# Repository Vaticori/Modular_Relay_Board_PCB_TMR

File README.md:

# Modular Relay Board TMR
A 4 channel relay board made for the Toronto Metropolitan Robotics team for higher voltage inputs to be switched using the onboard Teensy 4.1 MCU. 
I have linked the 3D model below, and a high resolution pdf of the schematic can be found in the repository. 

# [View Interactive 3D Model of my PCB!](https://skfb.ly/pACNG)

## Schematic

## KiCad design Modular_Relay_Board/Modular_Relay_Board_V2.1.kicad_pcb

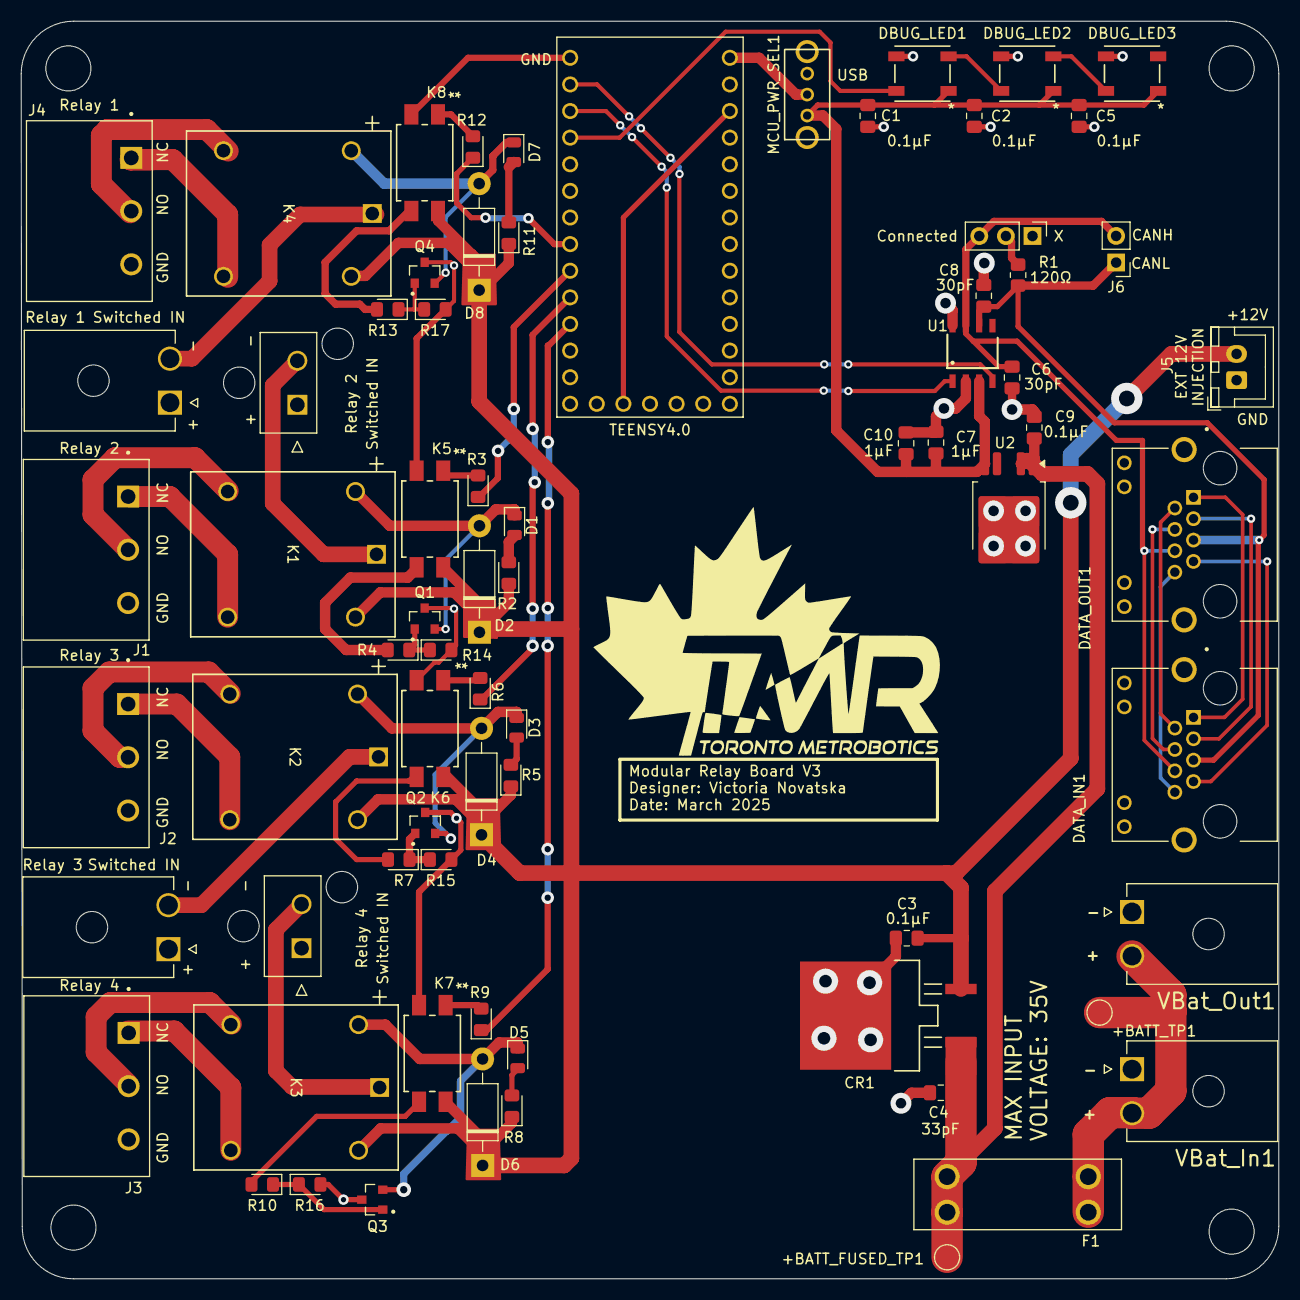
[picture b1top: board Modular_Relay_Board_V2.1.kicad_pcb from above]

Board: 2 copper layers, 120.0 x 120.0 mm, 73 parts (0 on the bottom side), 57 nets.

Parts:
+BATT_FUSED_TP1: TestPoint; TestPoint_Pad_D2.0mm
+BATT_TP1: TestPoint; TestPoint_Pad_D2.0mm
C1, C2, C3, C5, C7, C9: CL21B104KBCNNNC; C_0805_2012Metric_Pad1.18x1.45mm_HandSolder
C4: CC0805JRNPO9BN330; C_0805_2012Metric_Pad1.18x1.45mm_HandSolder
C6, C8: 0805CG300J500NT; C_0805_2012Metric_Pad1.18x1.45mm_HandSolder
C10: CL21B105KAFNFNE; C_0805_2012Metric_Pad1.18x1.45mm_HandSolder
CR1: C13456; D2PAK_STM
D1, D3, D5, D7: KT-0805Y; LED_0805_2012Metric
D2, D4, D6, D8: 1N4007; D_DO-41_SOD81_P10.16mm_Horizontal
DATA_IN1: MTJ-88ARX1-FSM-LG; ADAMTECH_MTJ-88ARX1-FSM-LG
DATA_OUT1: MTJ-88ARX1-FSM-LG; ADAMTECH_MTJ-88ARX1-FSM-LG
DBUG_LED1, DBUG_LED2, DBUG_LED3: COM-16347; COM-16347_SPK-M
F1: 3557-2; FUSE_3557-2
J1, J2, J3, J4: 1757255; PHOENIX_1757255
J5: JST XH; JST_XH_B2B-XH-A_1x02_P2.50mm_Vertical
J6: Conn_01x02_Pin; PinHeader_1x02_P2.54mm_Vertical
K1, K2, K3, K4: AZ943-1CH-12DE; AZ943-1CH_AMZ
K5, K6, K7, K8: LTV-816S-TA1-A; LTV-816S_LTO
MCU_PWR_SEL1: OS102011MS2QN1
Q1, Q2, Q3, Q4: 2N7002; TRANS_2N7002
R1: 0805W8F1200T5E; R_0805_2012Metric_Pad1.20x1.40mm_HandSolder
R2, R3, R4, R5, R6, R7, R8, R9, R10, R11, R12, R13: 0805W8F1001T5E; LED_0805_2012Metric_Pad1.15x1.40mm_HandSolder
R14, R15, R16, R17: 0805W8F1003T5E (SMT业务专用); LED_0805_2012Metric_Pad1.15x1.40mm_HandSolder
TEENSY4.0: DEV-15583; MODULE_DEV-15583
TerminatingResistorSwitch1: Conn_01x03; PinHeader_1x03_P2.54mm_Vertical
U1: TJA1050T CAN Transceiver1; SOT96-1
U2: C2846669; TO-252-4
VBat_In1: 1726480102; MOLEX_1726480102
VBat_Out1: 1726480102; MOLEX_1726480102
VPP_to_Relay1, VPP_to_Relay3: 1726480102; MOLEX_1726480102
VPP_to_Relay2, VPP_to_Relay4: 1726480102; 172647-0102

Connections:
+3.3V: TEENSY4.0.3.3V_1, TEENSY4.0.3.3V_2
+5V: C1.1, C2.1, C5.1, C7.1, C10.1, DBUG_LED1.1 (VDD), DBUG_LED2.1 (VDD), DBUG_LED3.1 (VDD), MCU_PWR_SEL1.1 (A), U1.3 (VCC), U2.5 (Q)
+12: C3.2, CR1.3 (OUTPUT), D2.1 (K), D4.1 (K), D6.1 (K), D8.1 (K), J5.2, K1.5, K2.5, K3.5, K4.5, K5.4, K6.4, K7.4, K8.4, R2.1, R5.1, R8.1, R11.1
+BATT: +BATT_TP1.1, F1.1_1, F1.1_2, VBat_In1.2, VBat_Out1.2
+BATT_FUSED: +BATT_FUSED_TP1.1, C4.1, C9.1, CR1.1 (INPUT), F1.2_1, F1.2_2, U2.1 (VI), U2.2 (EN)
/Relay Module 1/VPP: K4.1, VPP_to_Relay1.2
/Relay Module 2/VPP: K1.1, VPP_to_Relay2.2
/Relay Module 3/VPP: K2.1, VPP_to_Relay3.2
/Relay Module 4/VPP: K3.1, VPP_to_Relay4.2
CAN+: TEENSY4.0.0, U1.4 (RXD)
CAN-: TEENSY4.0.1, U1.1 (TXD)
CAN_H1: DATA_IN1.4, DATA_OUT1.4
CAN_H2: C6.1, DATA_IN1.6, DATA_OUT1.6, J6.2, TerminatingResistorSwitch1.3, U1.7 (CANH)
CAN_H3: DATA_IN1.8, DATA_OUT1.8
CAN_L1: DATA_IN1.3, DATA_OUT1.3
CAN_L2: C8.1, DATA_IN1.5, DATA_OUT1.5, J6.1, R1.1, U1.6 (CANL)
CAN_L3: DATA_IN1.7, DATA_OUT1.7
DEBUG_LED: DBUG_LED1.4 (DIN), TEENSY4.0.2
GND: C1.2, C2.2, C3.1, C4.2, C5.2, C6.2, C7.2, C8.2, C9.2, C10.2, CR1.2 (GROUND), DATA_IN1.SH1 (SHIELD), DATA_IN1.SH2 (SHIELD), DATA_OUT1.SH1 (SHIELD), DATA_OUT1.SH2 (SHIELD), DBUG_LED1.3 (VSS), DBUG_LED2.3 (VSS), DBUG_LED3.3 (VSS), J1.03, J2.03, J3.03, J4.03, J5.1, K5.2, K6.2, K7.2, K8.2, Q1.3, Q2.3, Q3.3, Q4.3, R14.2, R15.2, R16.2, R17.2, TEENSY4.0.G1, TEENSY4.0.G2, TEENSY4.0.G3, U1.2 (GND), U1.8 (S), U2.3 (GND), VBat_In1.1, VBat_Out1.1, VPP_to_Relay1.1, VPP_to_Relay2.1, VPP_to_Relay3.1, VPP_to_Relay4.1
unnamed: D1.2 (A), R2.2
unnamed: D1.1 (K), D2.2 (A), K1.2, Q1.2
unnamed: D3.2 (A), R5.2
unnamed: D3.1 (K), D4.2 (A), K2.2, Q2.2
unnamed: D5.2 (A), R8.2
unnamed: D5.1 (K), D6.2 (A), K3.2, Q3.2
unnamed: D7.2 (A), R11.2
unnamed: D7.1 (K), D8.2 (A), K4.2, Q4.2
unnamed: DBUG_LED1.2 (DOUT), DBUG_LED2.4 (DIN)
unnamed: DBUG_LED2.2 (DOUT), DBUG_LED3.4 (DIN)
unnamed: J1.01, K1.4
unnamed: J1.02, K1.3
unnamed: J2.01, K2.4
unnamed: J2.02, K2.3
unnamed: J3.01, K3.4
unnamed: J3.02, K3.3
unnamed: J4.01, K4.4
unnamed: J4.02, K4.3
unnamed: K5.1, R3.2
unnamed: K5.3, R4.2
unnamed: K6.1, R6.2
unnamed: K6.3, R7.2
unnamed: K7.1, R9.2
unnamed: K7.3, R10.2
unnamed: K8.1, R12.2
unnamed: K8.3, R13.2
unnamed: MCU_PWR_SEL1.2 (B), TEENSY4.0.VIN
unnamed: Q1.1, R4.1, R14.1
unnamed: Q2.1, R7.1, R15.1
unnamed: Q3.1, R10.1, R16.1
unnamed: Q4.1, R13.1, R17.1
unnamed: R1.2, TerminatingResistorSwitch1.2
RELAY_1: R12.1, TEENSY4.0.6
RELAY_2: R3.1, TEENSY4.0.7
RELAY_3: R6.1, TEENSY4.0.8
RELAY_4: R9.1, TEENSY4.0.9
UART1RX: DATA_IN1.2, DATA_OUT1.2
UART1TX: DATA_IN1.1, DATA_OUT1.1

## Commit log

2025-08-29 final
